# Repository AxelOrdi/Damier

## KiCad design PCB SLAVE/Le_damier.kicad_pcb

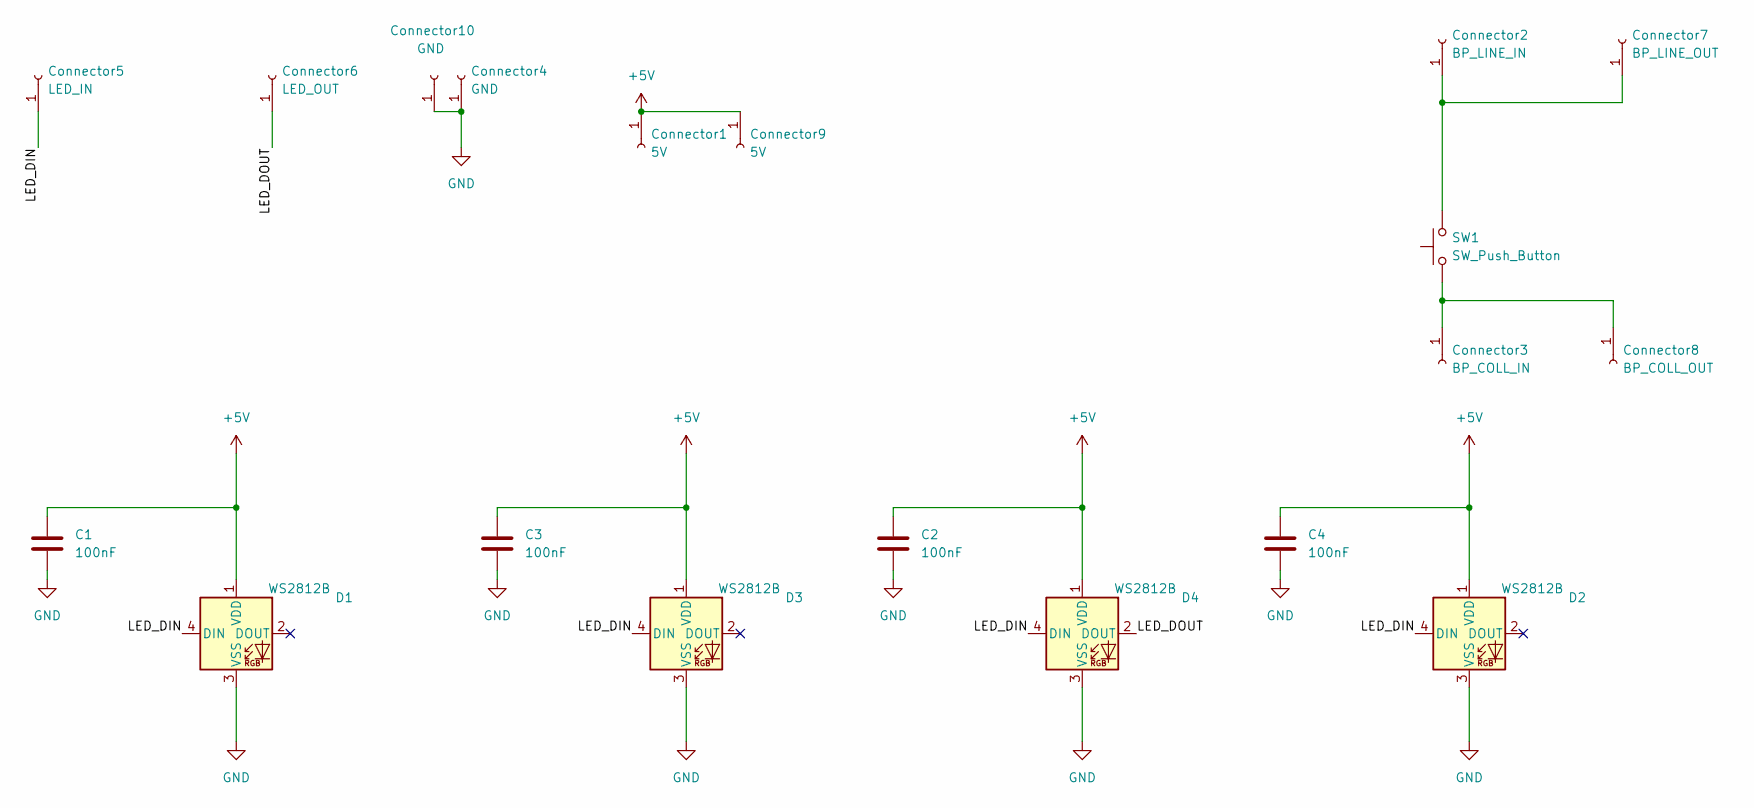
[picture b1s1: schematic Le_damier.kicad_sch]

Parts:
C1, C2, C3, C4: 100nF; C_1206_3216Metric
Connector1, Connector9: 5V; PinHeader_1x01_P2.54mm_Vertical
Connector2: BP_LINE_IN; PinHeader_1x01_P2.54mm_Vertical
Connector3: BP_COLL_IN; PinHeader_1x01_P2.54mm_Vertical
Connector4, Connector10: GND; PinHeader_1x01_P2.54mm_Vertical
Connector5: LED_IN; PinHeader_1x01_P2.54mm_Vertical
Connector6: LED_OUT; PinHeader_1x01_P2.54mm_Vertical
Connector7: BP_LINE_OUT; PinHeader_1x01_P2.54mm_Vertical
Connector8: BP_COLL_OUT; PinHeader_1x01_P2.54mm_Vertical
D1, D2, D3, D4: WS2812B; LED_WS2812B_PLCC4_5.0x5.0mm_P3.2mm
SW1: SW_Push_Button; SW_PUSH_6mm

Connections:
+5V: C1.1, C2.1, C3.1, C4.1, Connector1.1, Connector9.1, D1.1 (VDD), D2.1 (VDD), D3.1 (VDD), D4.1 (VDD)
/LED_DIN: Connector5.1, D1.4 (DIN), D2.4 (DIN), D3.4 (DIN), D4.4 (DIN)
/LED_DOUT: Connector6.1, D4.2 (DOUT)
GND: C1.2, C2.2, C3.2, C4.2, Connector4.1, Connector10.1, D1.3 (VSS), D2.3 (VSS), D3.3 (VSS), D4.3 (VSS)
unnamed: Connector2.1, Connector7.1, SW1.2
unnamed: Connector3.1, Connector8.1, SW1.1

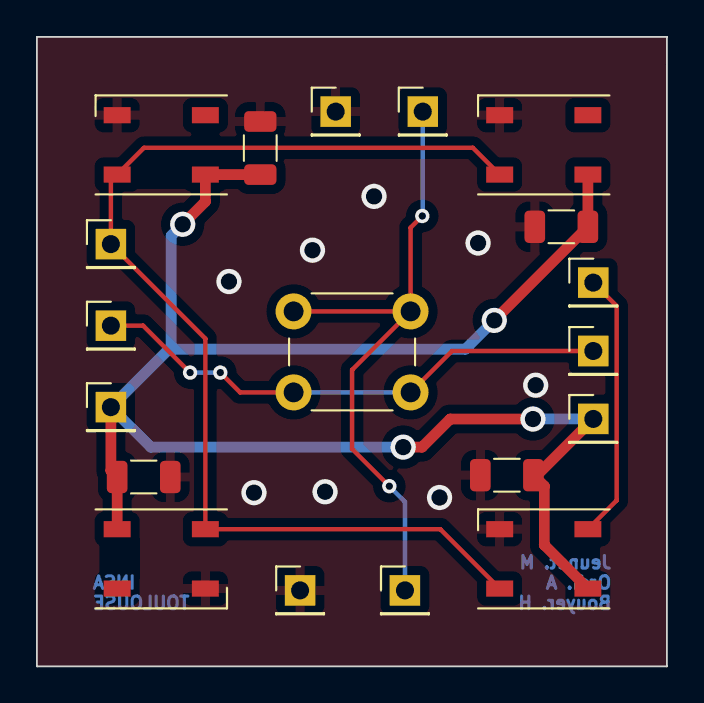
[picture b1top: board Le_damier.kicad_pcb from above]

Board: 2 copper layers, 35.0 x 35.0 mm, 19 parts (0 on the bottom side), 6 nets.

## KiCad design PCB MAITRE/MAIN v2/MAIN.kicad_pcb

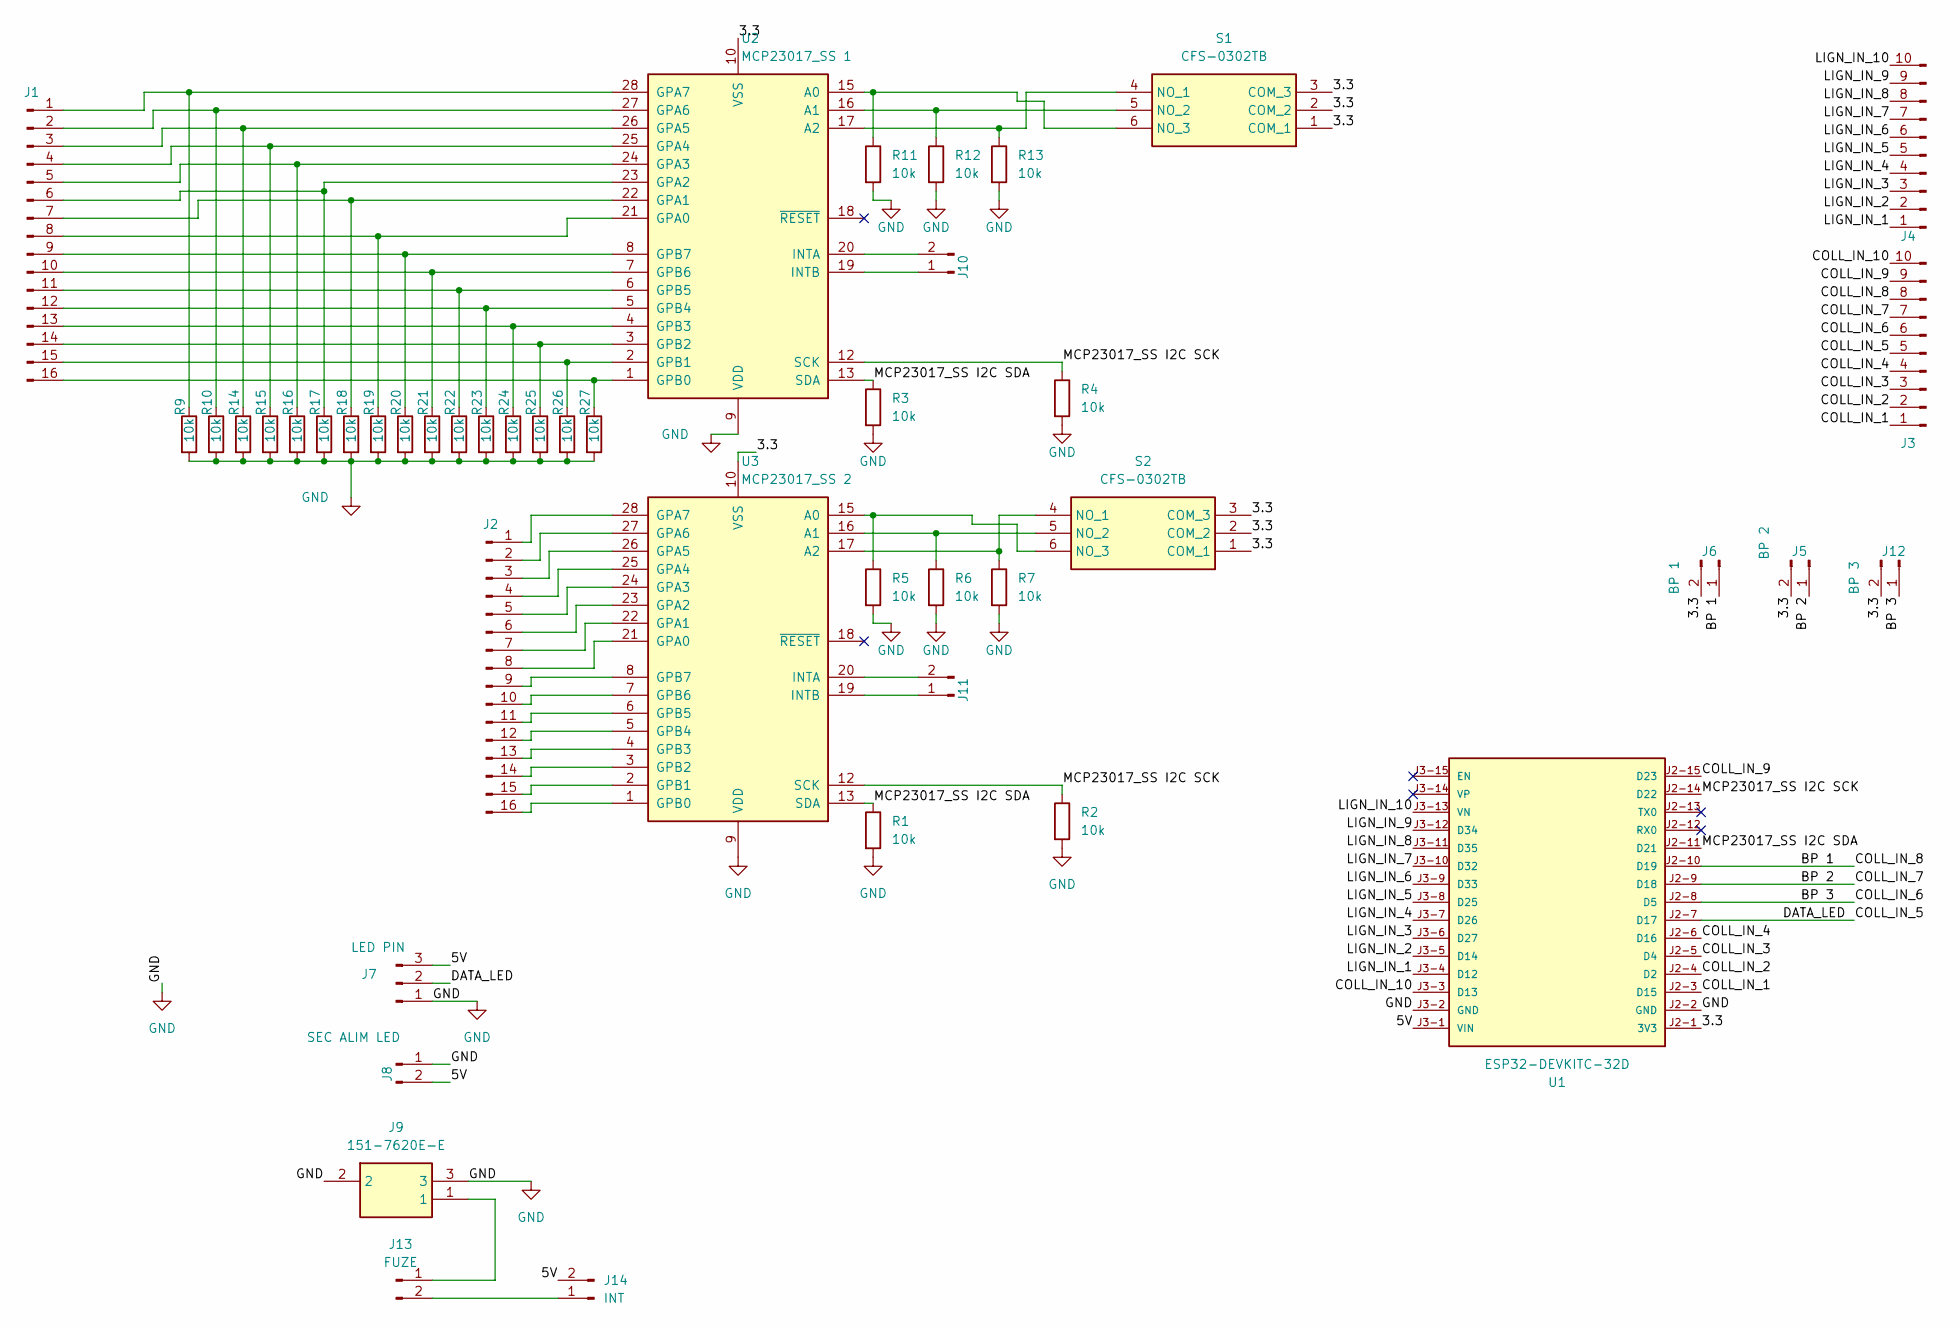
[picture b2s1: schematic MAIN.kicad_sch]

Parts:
J1, J2: Conn_01x16_Pin; PinHeader_1x16_P2.54mm_Vertical
J3, J4: Conn_01x10_Pin; PinHeader_1x10_P2.54mm_Vertical
J5: BP 2; PinHeader_1x02_P2.54mm_Vertical
J6: BP 1; PinHeader_1x02_P2.54mm_Vertical
J7: LED PIN; SolderWire-2.5sqmm_1x03_P8.8mm_D2.4mm_OD4.4mm
J8: SEC ALIM LED; SolderWire-2.5sqmm_1x02_P8.8mm_D2.4mm_OD4.4mm
J9: 151-7620E-E; 1517620EE; Mouser Part Number 151-7620E-E
J10: INTAB MCP23017 1; PinHeader_1x02_P2.54mm_Vertical
J11: INTAB MCP23017 2; PinHeader_1x02_P2.54mm_Vertical
J12: BP 3; PinHeader_1x02_P2.54mm_Vertical
J13: FUZE; SolderWire-2.5sqmm_1x02_P8.8mm_D2.4mm_OD4.4mm
J14: INT; SolderWire-2.5sqmm_1x02_P8.8mm_D2.4mm_OD4.4mm
R1, R2, R3, R4, R5, R6, R7, R9, R10, R11, R12, R13, R14, R15, R16, R17, R18, R19, R20, R21, R22, R23, R24, R25, R26, R27: 10k; R_1206_3216Metric
S1, S2: CFS-0302TB; CFS0302TB; Mouser Part Number 229-CFS-0302TB
U1: ESP32-DEVKITC-32D; MODULE_ESP32-DEVKITC-32D; PARTREV V4
U2: MCP23017_SS 1; SSOP-28_5.3x10.2mm_P0.65mm
U3: MCP23017_SS 2; SSOP-28_5.3x10.2mm_P0.65mm

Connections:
/3.3: J5.2, J6.2, J12.2, S1.1 (COM_1), S1.2 (COM_2), S1.3 (COM_3), S2.1 (COM_1), S2.2 (COM_2), S2.3 (COM_3), U1.J2-1 (3V3), U2.10 (VSS), U3.10 (VSS)
/5V: J7.3, J8.2, J14.2, U1.J3-1 (VIN)
/BP 1: J3.8, J6.1, U1.J2-10 (D19)
/BP 2: J3.7, J5.1, U1.J2-9 (D18)
/BP 3: J3.6, J12.1, U1.J2-8 (D5)
/COLL_IN_1: J3.1, U1.J2-3 (D15)
/COLL_IN_2: J3.2, U1.J2-4 (D2)
/COLL_IN_3: J3.3, U1.J2-5 (D4)
/COLL_IN_4: J3.4, U1.J2-6 (D16)
/COLL_IN_5: J3.5, J7.2, U1.J2-7 (D17)
/COLL_IN_9: J3.9, U1.J2-15 (D23)
/COLL_IN_10: J3.10, U1.J3-3 (D13)
/LIGN_IN_1: J4.1, U1.J3-4 (D12)
/LIGN_IN_2: J4.2, U1.J3-5 (D14)
/LIGN_IN_3: J4.3, U1.J3-6 (D27)
/LIGN_IN_4: J4.4, U1.J3-7 (D26)
/LIGN_IN_5: J4.5, U1.J3-8 (D25)
/LIGN_IN_6: J4.6, U1.J3-9 (D33)
/LIGN_IN_7: J4.7, U1.J3-10 (D32)
/LIGN_IN_8: J4.8, U1.J3-11 (D35)
/LIGN_IN_9: J4.9, U1.J3-12 (D34)
/LIGN_IN_10: J4.10, U1.J3-13 (VN)
/MCP23017_SS I2C SCK: R2.1, R4.1, U1.J2-14 (D22), U2.12 (SCK), U3.12 (SCK)
/MCP23017_SS I2C SDA: R1.1, R3.1, U1.J2-11 (D21), U2.13 (SDA), U3.13 (SDA)
GND: J7.1, J8.1, J9.2, J9.3, R1.2, R2.2, R3.2, R4.2, R5.2, R6.2, R7.2, R9.2, R10.2, R11.2, R12.2, R13.2, R14.2, R15.2, R16.2, R17.2, R18.2, R19.2, R20.2, R21.2, R22.2, R23.2, R24.2, R25.2, R26.2, R27.2, U1.J2-2 (GND), U1.J3-2 (GND), U2.9 (VDD), U3.9 (VDD)
unnamed: J1.1, R9.1, U2.28 (GPA7)
unnamed: J1.2, R10.1, U2.27 (GPA6)
unnamed: J1.3, R14.1, U2.26 (GPA5)
unnamed: J1.4, R15.1, U2.25 (GPA4)
unnamed: J1.5, R16.1, U2.24 (GPA3)
unnamed: J1.6, R17.1, U2.23 (GPA2)
unnamed: J1.7, R18.1, U2.22 (GPA1)
unnamed: J1.8, R19.1, U2.21 (GPA0)
unnamed: J1.9, R20.1, U2.8 (GPB7)
unnamed: J1.10, R21.1, U2.7 (GPB6)
unnamed: J1.11, R22.1, U2.6 (GPB5)
unnamed: J1.12, R23.1, U2.5 (GPB4)
unnamed: J1.13, R24.1, U2.4 (GPB3)
unnamed: J1.14, R25.1, U2.3 (GPB2)
unnamed: J1.15, R26.1, U2.2 (GPB1)
unnamed: J1.16, R27.1, U2.1 (GPB0)
unnamed: J2.1, U3.28 (GPA7)
unnamed: J2.2, U3.27 (GPA6)
unnamed: J2.3, U3.26 (GPA5)
unnamed: J2.4, U3.25 (GPA4)
unnamed: J2.5, U3.24 (GPA3)
unnamed: J2.6, U3.23 (GPA2)
unnamed: J2.7, U3.22 (GPA1)
unnamed: J2.8, U3.21 (GPA0)
unnamed: J2.9, U3.8 (GPB7)
unnamed: J2.10, U3.7 (GPB6)
unnamed: J2.11, U3.6 (GPB5)
unnamed: J2.12, U3.5 (GPB4)
unnamed: J2.13, U3.4 (GPB3)
unnamed: J2.14, U3.3 (GPB2)
unnamed: J2.15, U3.2 (GPB1)
unnamed: J2.16, U3.1 (GPB0)
unnamed: J10.1, U2.19 (INTB)
unnamed: J10.2, U2.20 (INTA)
unnamed: J11.1, U3.19 (INTB)
unnamed: J11.2, U3.20 (INTA)
unnamed: J9.1, J13.1
unnamed: J13.2, J14.1
unnamed: R13.1, S1.4 (NO_1), U2.17 (A2)
unnamed: R12.1, S1.5 (NO_2), U2.16 (A1)
unnamed: R11.1, S1.6 (NO_3), U2.15 (A0)
unnamed: R7.1, S2.4 (NO_1), U3.17 (A2)
unnamed: R6.1, S2.5 (NO_2), U3.16 (A1)
unnamed: R5.1, S2.6 (NO_3), U3.15 (A0)

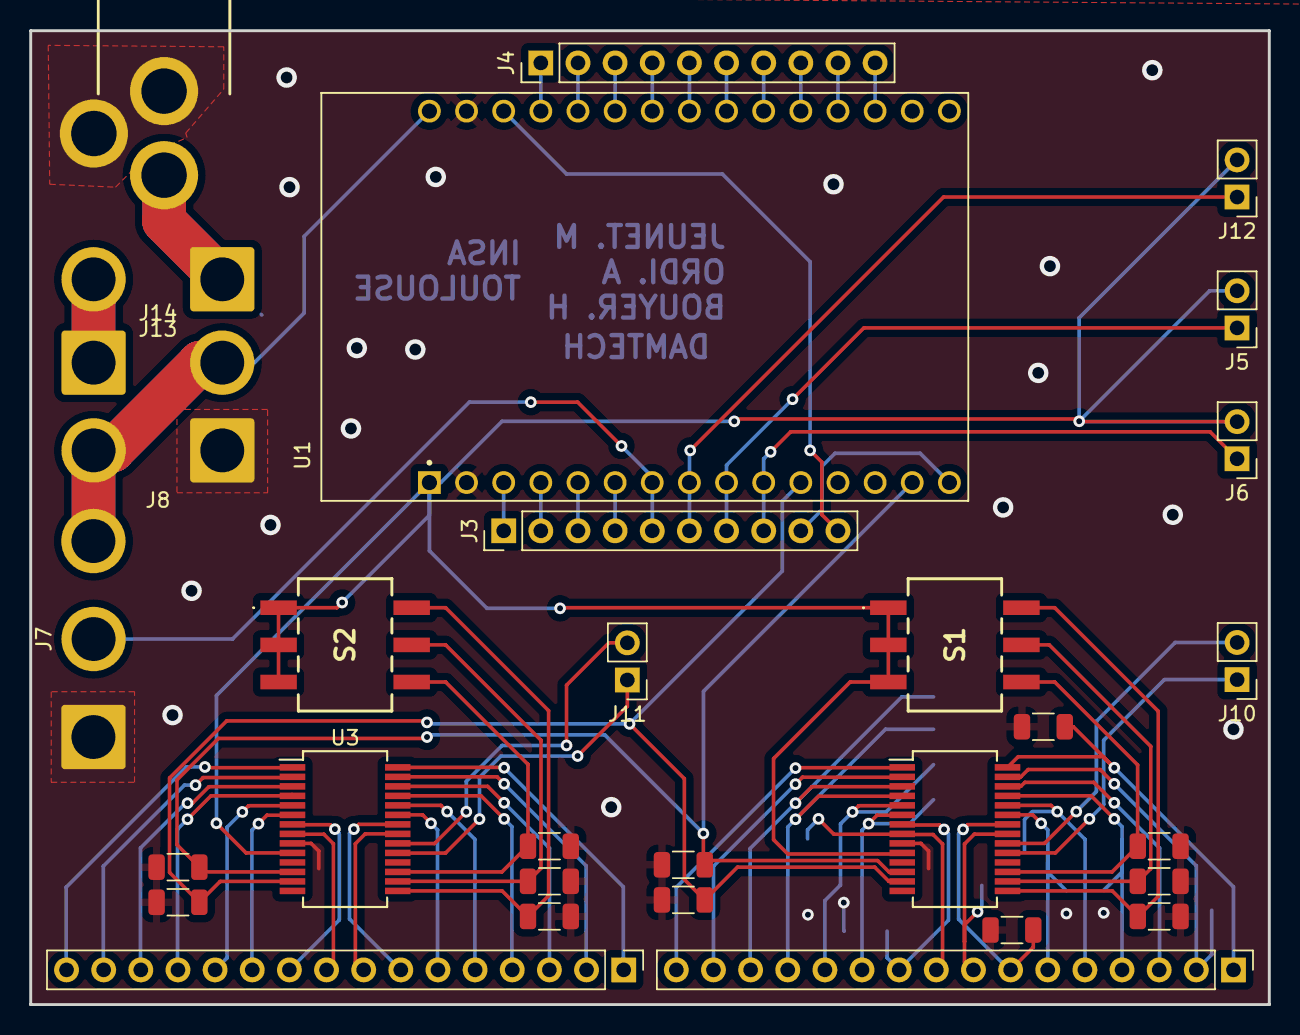
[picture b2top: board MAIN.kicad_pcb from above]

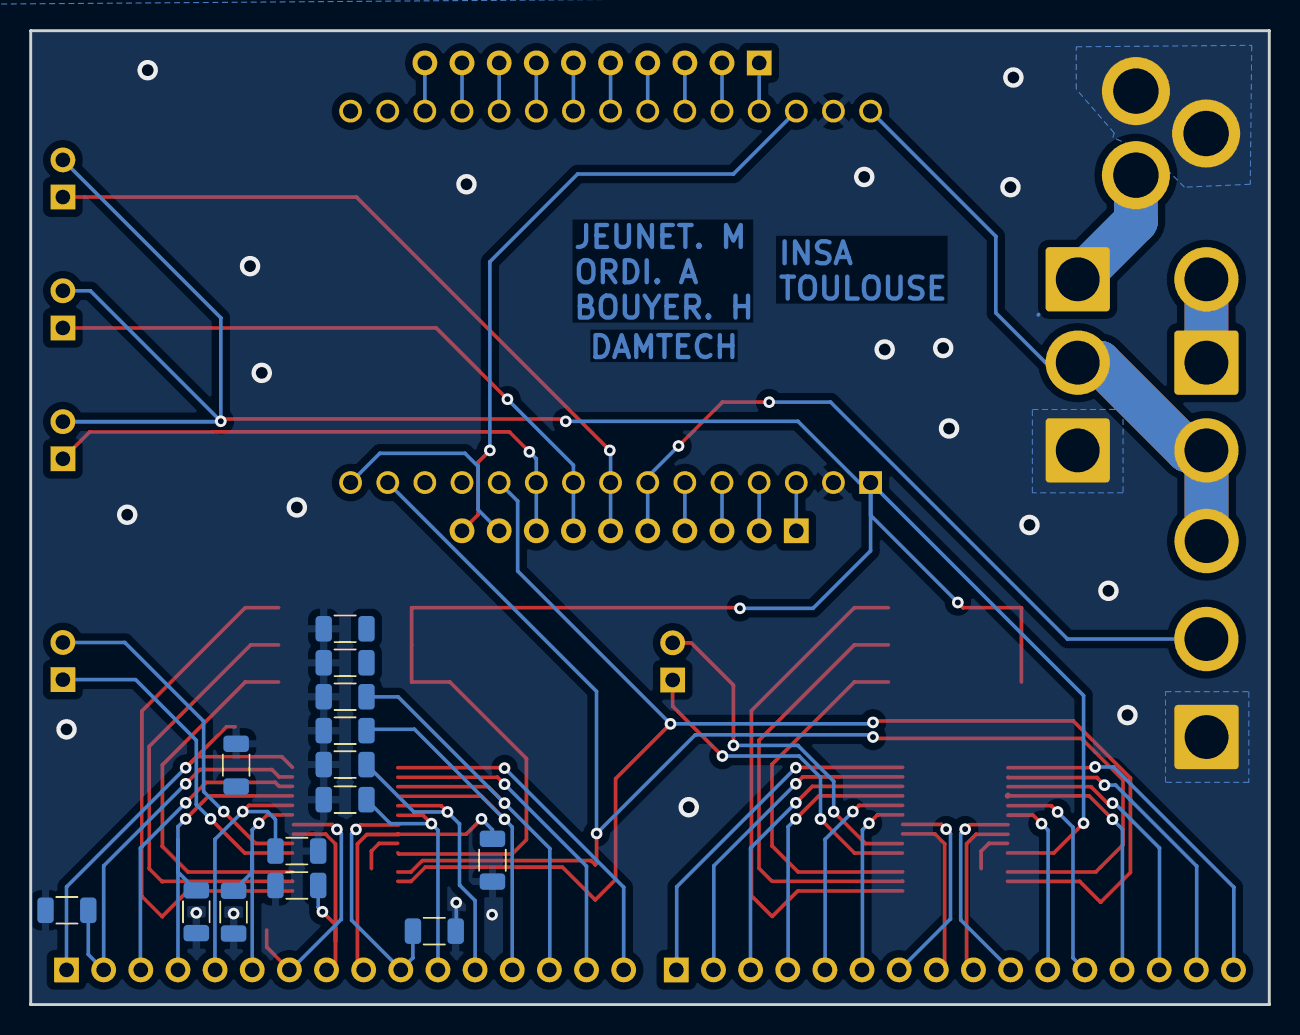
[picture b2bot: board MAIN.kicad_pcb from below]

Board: 2 copper layers, 84.7 x 66.6 mm, 45 parts (14 on the bottom side), 69 nets.

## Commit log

2023-12-13 changer la position des pions créer dans Jeu de Dame pour la condition de fin de jeu
2023-12-15 Changement des coordonnées dans jeu_de_dame Etat 7. +Il est peut etre nécessaire de vérifier si cet état doit rammener a etat 6 ou 3
